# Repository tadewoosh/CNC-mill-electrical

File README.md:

# CNC router/mill: electrical
The electrical part of the CNC router/mill project.

This repo contains the files needed for construction of a custom motion controller **based on the [GRBL 1.1](https://github.com/gnea/grbl) project**. If you don't want to make your own PCB you can use any GRBL-compatible motion controller - same basic principles of operation will apply.

## Table of contents

  * [Block diagram](#block-diagram)
  * [Motion controller](#motion-controller)
    + [Why not Arduino?](#why-not-arduino-)
    + [Detailed specification](#detailed-specification)
    + [GRBL Settings](#grbl-settings)
  * [Inputs wiring](#inputs-wiring)
    + [Limit switches](#limit-switches)
    + [Probe](#Probe)
    + [User buttons](#user-buttons)
  * [Motor Drivers](#motor-drivers)
    + [Driver configuration](#driver-configuration)
    + [Driver connection](#driver-connection)
  * [Inverter and Spindle](#inverter-and-spindle)
    + [Inverter connection](#inverter-connection)
    + [Spindle cooling](#spindle-cooling)
  * [Software for G-Code streaming](#software-for-g-code-streaming)
    + [Candle](#candle)
    + [GRBL Panel](#grbl-panel)

## Block diagram

## Motion controller

### Why not Arduino?
The main controller board is an AVR **ATmega8** based device aiming to replace the Arduino board as the motion controller. The reason why one might want to use this board instead of Arduino is that it provides:
* Galvanic insulation of the machine and the PC
* Robust power circuitry
* Robust, edge mounted connectors suitable for more "industrial" use
* Additional noise-reducing and LPF circuitry for the inputs and outputs
* A high-voltage output for the coolant valve relay

The Eagle project files are hosted in this repository along with the CAM configuration and its output (GERBER, drillfiles etc.) allowing for the easy PCB manufacturing/ordering.

In order to program a blank AVR chip with GRBL one needs first to obtain the Arduino bootloader allowing to update the frmware via the serial port from Arduino IDE.

### Detailed specification

* Up to 36V DC supply voltage when using **TSR 1-2450** DC-DC, otherwise **7805** linear regulator specification applies.
* Reverse power supply protection
* Reset switch
* ISP connector (*NOTE: Programming using ISP shlud not be conducted when the spindle inverter is connected.*)
* Debug serial commincation port with 5V tap
* USB to serial converter based on FTDI with optoisolation
* 3 sets of STEP/DIR/ENABLE connectors for stepper drivers with LED indicators
* User switches inputs (active low, with debouncing circuitry): ABORT, HOLD, START
* Probe input with debouncing circuitry and LED indication
* 3 limit switches inputs, active low, with debouncing circuitry and LED indication
* High voltage (supply), high current (1A) output for driving the coolant relay with Shottky protection (for the control of the tool cooling - rarely used for woodworking)
* PWM or analog (using LPF) 0-5V output for spindle speed and direction control with LED indication
* Simple and easy to hand-solder 100x50 mm two-layer board with 3mm holes in the corners for ease of mounting. 

### GRBL Settings
TODO: 

GRBL Settings

## Inputs wiring
### Limit switches
TODO:

Limit switches wiring

### Probe
TODO:

Probe wiring

### User buttons
TODO:

User Buttons wiring

## Motor Drivers

The **2DM556S** 4.2A RMS drivers are used.

### Driver configuration

* Current limiter on the driver is set to 3,31A in order to drive the **60HS100-3504A08-D24** 4,3N.m stepper motors. This is not the maximum current (3.5A) for the motors, but in order to keep them from overheating during some long sessions this needed to be lowered.
* Microstepping is set to "4000 Steps per revolution" accoding to the chineese maunfacturer. In real world combined with 1,8 sdegree mechanical resolution of the stepper and 5mm/turn of the ballscrew on each axis returns a resolution of 800 steps/mm. That means a theoretical resolution per step is 1.25 um which is absurd, yet it probably helps a bit with the smoothnes.
* Standby current is set, so when the motor is not in motion the current is lowered. This helps with overheating and I have not seen any adverse effects on the quality of the cuts.
* Smoothnes settings seem not to affect the operation nor the sound at all so I have turned it off. The speed ramps are calculated in the motion controller and they work OK. 

### Driver connection

The cabling connecting all the low-power signals from motion controller to the driver should be as short as possible. Shielding and grounding should be sound in order to avoid EMC interference with high-current lines. Pay special notice to the location of the inverter-to-spindle cable (which should be shielded in its own right) since it is the devil of such application. Calculate the correct cable diameters in order to reduce voltage drops on the high-current lines. 

The drivers heated up very slightly during prolonged operation, the passive cooling of their ribbed cases seems sufficient.

## Inverter and Spindle

A chineese set of inverter and spindle is used. The rated power of both is 2.2kW.

The inverter model is **YL620-A-2.2kW**. It is powered by a single-phase 230V mains.

### Inverter connection

TODO: 

Inverter Connection

### Spindle cooling

The spindle is water-cooled, so I made a temperature monitoring system from an old graphic-lcd project based on another AVR and here is what it does:
* measures the temperatures of the ingoing and outgoing coolant using **DS18B20** 1-wire digital thermometers
* measures the flow of the coolant using a simple **YF-S201** flow-meter
* calculates the thermal power gathered by the coolant
* displays calculated values live on the 128x64 LCD
* watches for ovearheat and low-flow conditions in order to alert the operator, pause the program and disable the spindle

## Software for G-Code streaming
### Candle
TODO:

Candle description

### GRBL Panel
TODO:

GRBL Panel description

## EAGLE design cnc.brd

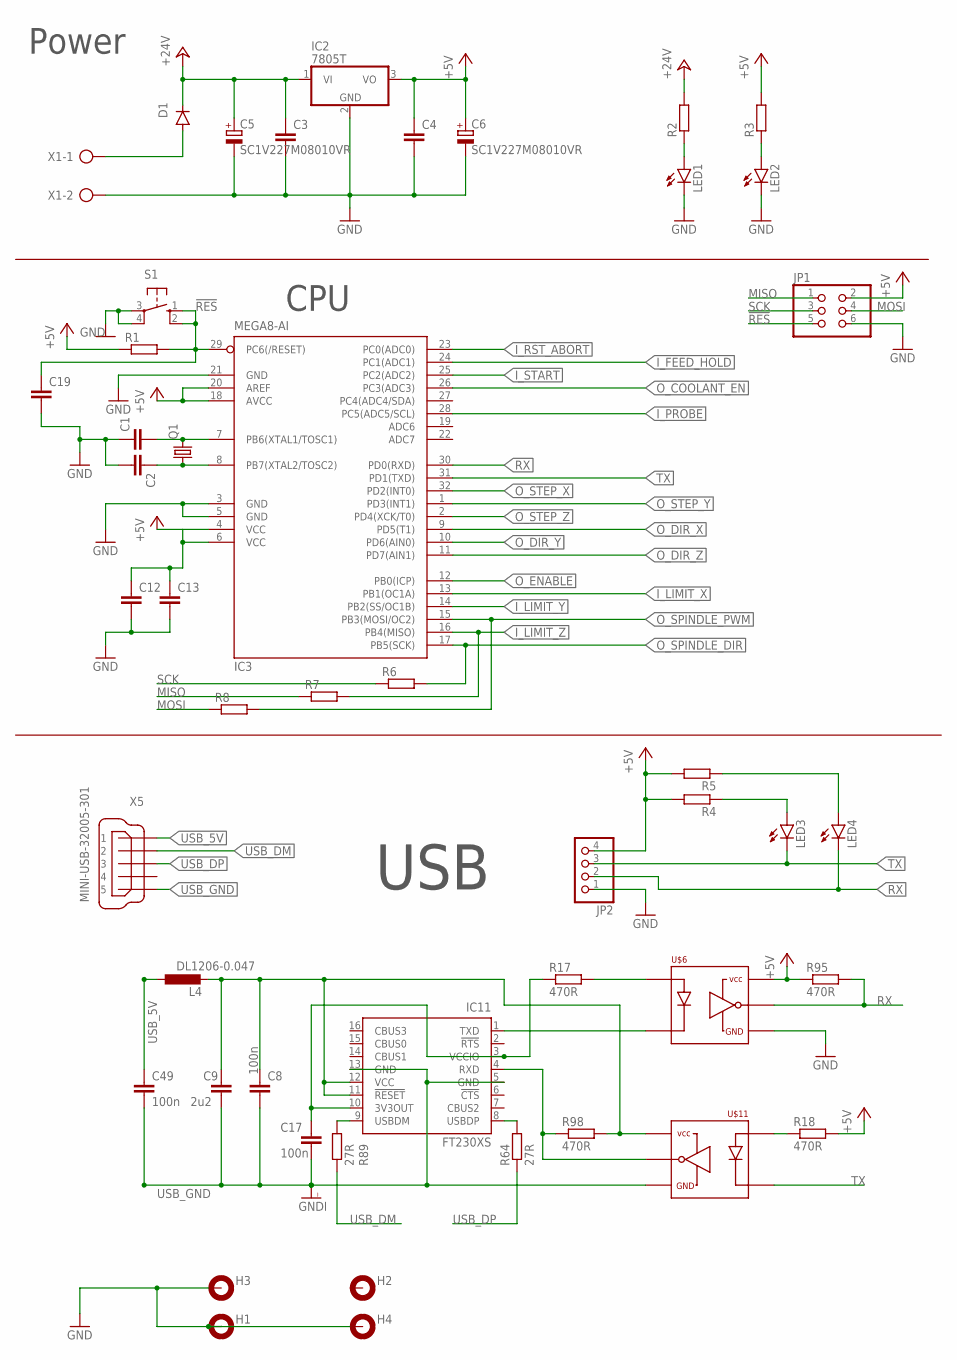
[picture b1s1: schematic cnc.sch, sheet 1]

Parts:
C1, C2, C3, C4, C12, C13, C19: C-EUC0603; C0603
C5, C6: SC1V227M08010VR; 150CLZ-0810
C8, C17, C49: 100n; C0603
C9: 2u2; C0603
D1: DIODE-DO-214AC; DO-214AC
H1, H2, H3, H4: MOUNT-PAD-ROUND3.0; 3,0-PAD
IC2: 7805T; TO220H
IC3: MEGA8-AI; TQFP32-08
IC11: FT230XS; SSOP16
JP1: PINHD-2X3; 2X03
JP2: PINHD-1X4; 1X04
L4: DL1206-0.047; L3225P
LED1, LED2: LEDCHIPLED_0805; CHIPLED_0805
LED3, LED4: LEDCHIPLED_0603; CHIPLED_0603
Q1: CRYSTALHC49S; HC49/S
R1, R2, R3, R4, R5, R6, R7, R8: R-EU_R0603; R0603
R17, R18, R95, R98: 470R; R0603
R64, R89: 27R; R0603
S1: 10-XX; B3F-10XX
U$6, U$11: TLP2362; SO-6
X1: AK500/2
X5: MINI-USB-32005-301; 32005-301

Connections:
!RES: C19.1, IC3.29 (PC6(/RESET)), JP1.5, R1.2, S1.1 (S), S1.2 (S1)
+5V: C4.1, C6.+, C12.1, C13.1, IC2.3 (VO), IC3.4 (VCC), IC3.6 (VCC), IC3.18 (AVCC), IC3.20 (AREF), JP1.2, JP2.4, R1.1, R3.2, R4.2, R5.2, R18.2, R95.1, U$6.6; also elsewhere on the board
+24V: C3.1, C5.+, D1.C, IC2.1 (VI), R2.2; also elsewhere on the board
FHBGVFC: C8.1, C9.1, IC11.11 (!RESET), IC11.12 (VCC), L4.2, R98.2, U$11.6
GND: C1.1, C2.2, C3.2, C4.2, C5.-, C6.-, C12.2, C13.2, C19.2, H1.B3,0, H3.B3,0, H4.B3,0, IC2.2 (GND), IC3.3 (GND), IC3.5 (GND), IC3.21 (GND), JP1.6, JP2.1, LED1.C, LED2.C, S1.3, S1.4 (P1), U$6.4, X1.2; also elsewhere on the board
I_FEED_HOLD: IC3.24 (PC1(ADC1)); also elsewhere on the board
I_LIMIT_X: IC3.13 (PB1(OC1A)); also elsewhere on the board
I_LIMIT_Y: IC3.14 (PB2(SS/OC1B)); also elsewhere on the board
I_LIMIT_Z: IC3.16 (PB4(MISO)), R7.2; also elsewhere on the board
I_PROBE: IC3.28 (PC5(ADC5/SCL)); also elsewhere on the board
I_RST_ABORT: IC3.23 (PC0(ADC0)); also elsewhere on the board
I_START: IC3.25 (PC2(ADC2)); also elsewhere on the board
MISO: JP1.1, R7.1
MOSI: JP1.4, R8.1
unnamed: D1.A, X1.1
unnamed: LED1.A, R2.1
unnamed: LED2.A, R3.1
unnamed: LED3.A, R4.1
unnamed: LED4.A, R5.1
unnamed: C1.2, IC3.7 (PB6(XTAL1/TOSC1)), Q1.2
unnamed: C2.1, IC3.8 (PB7(XTAL2/TOSC2)), Q1.1
unnamed: C17.1, IC11.3 (VCCIO), IC11.10 (3V3OUT), R17.1
unnamed: IC11.1 (TXD), U$6.3
unnamed: IC11.9 (USBDM), R89.2
unnamed: IC11.8 (USBDP), R64.2
unnamed: R17.2, U$6.1
unnamed: IC11.4 (RXD), R98.1, U$11.5
unnamed: R18.1, U$11.1
O_COOLANT_EN: IC3.26 (PC3(ADC3)); also elsewhere on the board
O_DIR_X: IC3.9 (PD5(T1)); also elsewhere on the board
O_DIR_Y: IC3.10 (PD6(AIN0)); also elsewhere on the board
O_DIR_Z: IC3.11 (PD7(AIN1)); also elsewhere on the board
O_ENABLE: IC3.12 (PB0(ICP)); also elsewhere on the board
O_SPINDLE_DIR: IC3.17 (PB5(SCK)), R6.2; also elsewhere on the board
O_SPINDLE_PWM: IC3.15 (PB3(MOSI/OC2)), R8.2; also elsewhere on the board
O_STEP_X: IC3.32 (PD2(INT0)); also elsewhere on the board
O_STEP_Y: IC3.1 (PD3(INT1)); also elsewhere on the board
O_STEP_Z: IC3.2 (PD4(XCK/T0)); also elsewhere on the board
RX: IC3.30 (PD0(RXD)), JP2.2, LED4.C, R95.2, U$6.5
SCK: JP1.3, R6.1
TX: IC3.31 (PD1(TXD)), JP2.3, LED3.C, U$11.3
USB_5V: C49.1, L4.1, X5.1
USB_DM: R89.1, X5.2
USB_DP: R64.1, X5.3
USB_GND: C8.2, C9.2, C17.2, C49.2, IC11.5 (GND), IC11.13 (GND), U$11.4, X5.5

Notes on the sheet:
Power
CPU
USB

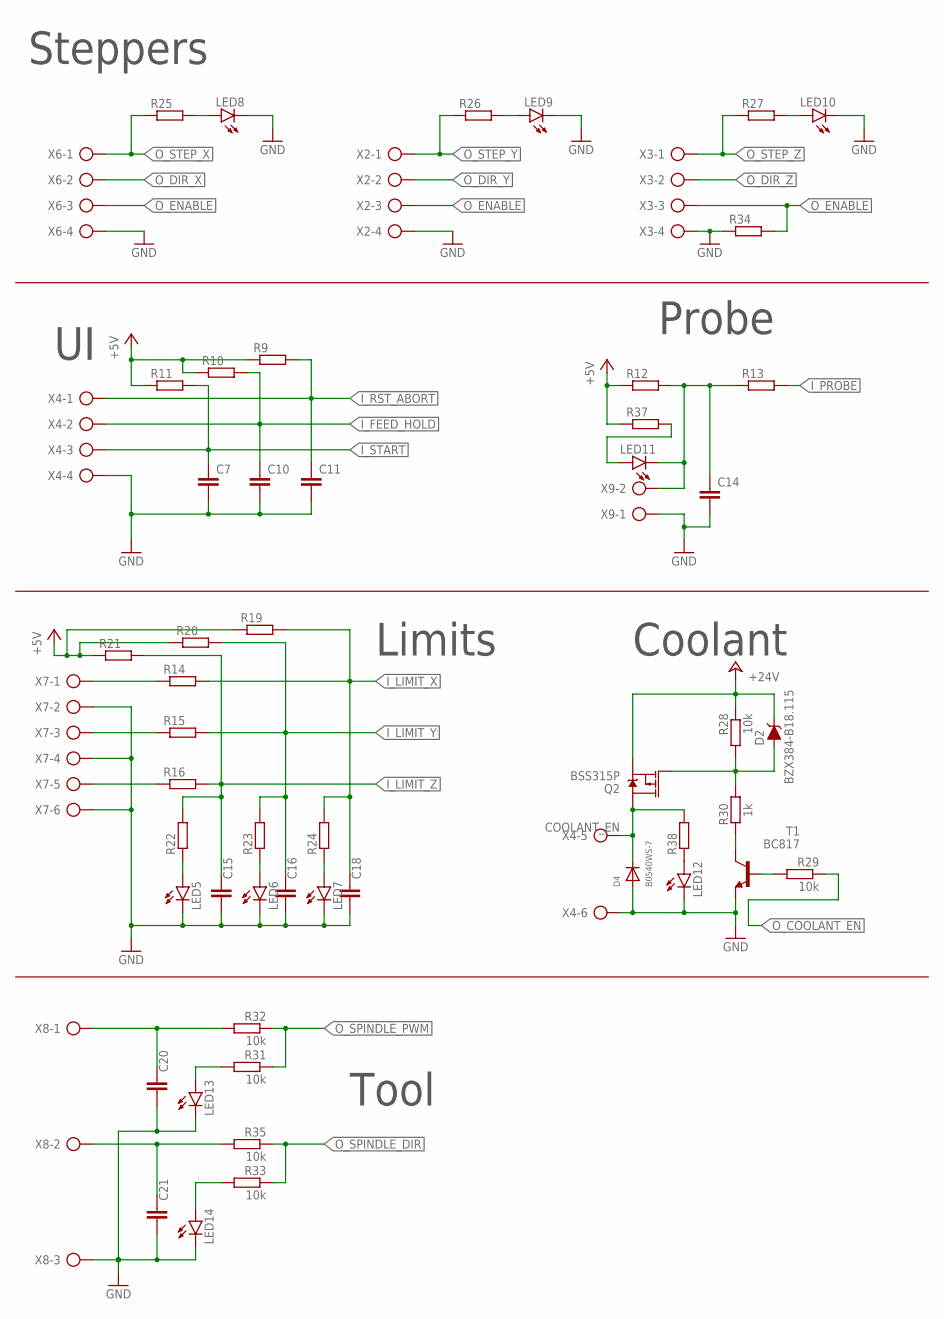
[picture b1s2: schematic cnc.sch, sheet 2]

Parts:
C7, C10, C11, C14, C15, C16, C18, C20, C21: C-EUC0603; C0603
D2: BZX384-B18.115; SOD-323
D4: B0540WS-7; SOD-323F
LED5, LED6, LED7, LED8, LED9, LED10, LED11, LED12, LED13, LED14: LEDCHIPLED_0603; CHIPLED_0603
Q2: BSS315P; SOT23-3
R9, R10, R11, R12, R13, R14, R15, R16, R19, R20, R21, R22, R23, R24, R25, R26, R27, R34, R37, R38: R-EU_R0603; R0603
R28, R29, R31, R32, R33, R35: 10k; R0603
R30: 1k; R0603
T1: BC817; SOT23-BEC
X2, X3, X6: AK500/4
X4, X7: AK500/6
X8: AK500/3
X9: AK500/2

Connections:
+5V: R9.1, R10.1, R11.1, R12.1, R19.1, R20.1, R21.1, R37.1; also elsewhere on the board
+24V: D2.C, Q2.2 (S), R28.1; also elsewhere on the board
COOLANT_EN: D4.C, Q2.3 (D), R38.2, X4.5
GND: C7.2, C10.2, C11.2, C14.2, C15.2, C16.2, C18.2, C20.2, C21.2, D4.A, LED5.C, LED6.C, LED7.C, LED8.C, LED9.C, LED10.C, LED12.C, LED13.C, LED14.C, R34.1, T1.E, X2.4, X3.4, X4.4, X4.6, X6.4, X7.2, X7.4, X7.6, X8.3, X9.1; also elsewhere on the board
I_FEED_HOLD: C10.1, R10.2, X4.2; also elsewhere on the board
I_LIMIT_X: C18.1, R14.2, R19.2, R24.2; also elsewhere on the board
I_LIMIT_Y: C16.1, R15.2, R20.2, R23.2; also elsewhere on the board
I_LIMIT_Z: C15.1, R16.2, R21.2, R22.2; also elsewhere on the board
I_PROBE: R13.2; also elsewhere on the board
I_RST_ABORT: C11.1, R9.2, X4.1; also elsewhere on the board
I_START: C7.1, R11.2, X4.3; also elsewhere on the board
unnamed: C14.1, LED11.C, R12.2, R13.1, X9.2
unnamed: R16.1, X7.5
unnamed: R15.1, X7.3
unnamed: R14.1, X7.1
unnamed: LED8.A, R25.2
unnamed: LED5.A, R22.1
unnamed: R30.2, T1.C
unnamed: LED6.A, R23.1
unnamed: LED9.A, R26.2
unnamed: LED7.A, R24.1
unnamed: LED14.A, R33.2
unnamed: LED13.A, R31.2
unnamed: LED10.A, R27.2
unnamed: C20.1, R32.2, X8.1
unnamed: C21.1, R35.2, X8.2
unnamed: LED11.A, R37.2
unnamed: LED12.A, R38.1
unnamed: D2.A, Q2.1 (G), R28.2, R30.1
unnamed: R29.2, T1.B
O_COOLANT_EN: R29.1; also elsewhere on the board
O_DIR_X: X6.2; also elsewhere on the board
O_DIR_Y: X2.2; also elsewhere on the board
O_DIR_Z: X3.2; also elsewhere on the board
O_ENABLE: R34.2, X2.3, X3.3, X6.3; also elsewhere on the board
O_SPINDLE_DIR: R33.1, R35.1; also elsewhere on the board
O_SPINDLE_PWM: R31.1, R32.1; also elsewhere on the board
O_STEP_X: R25.1, X6.1; also elsewhere on the board
O_STEP_Y: R26.1, X2.1; also elsewhere on the board
O_STEP_Z: R27.1, X3.1; also elsewhere on the board

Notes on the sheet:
Steppers
Limits
Tool
Coolant
Probe

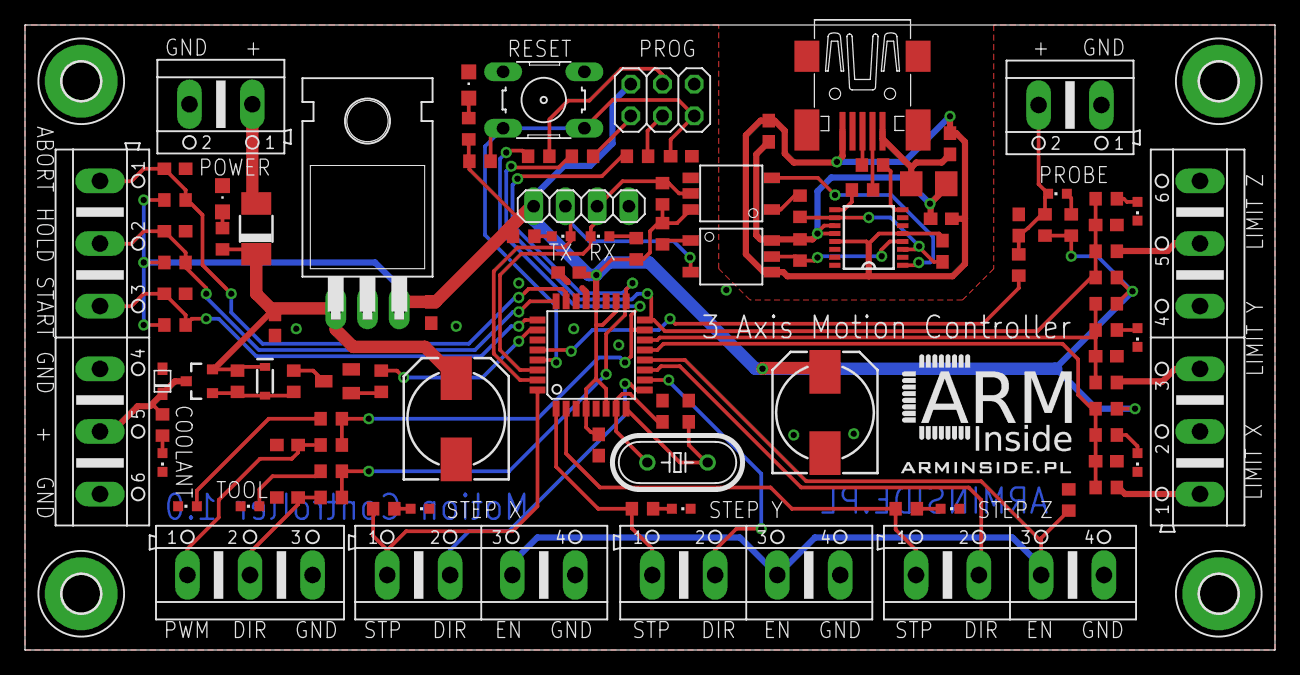
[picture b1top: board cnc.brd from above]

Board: 2 copper layers, 100.0 x 50.0 mm, 105 parts (0 on the bottom side), 65 nets.

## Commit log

2020-09-04 added Images
2020-09-04 diagram added
2020-09-04 added ignored
2020-09-04 CAM output
2020-09-04 images added
2020-09-04 schematic
2020-09-04 driver connection
2020-09-04 cooling
2020-10-19 Created project
2020-10-19 Imported from https://tadewoosh@github.com/tadewoosh/CNC-mill-electrical.git

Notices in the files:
parts and their libraries:
SparkFun-DiscreteSemi: Licensing: Creative Commons ShareAlike 4.0 International - https://creativecommons.org/licenses/by-sa/4.0
